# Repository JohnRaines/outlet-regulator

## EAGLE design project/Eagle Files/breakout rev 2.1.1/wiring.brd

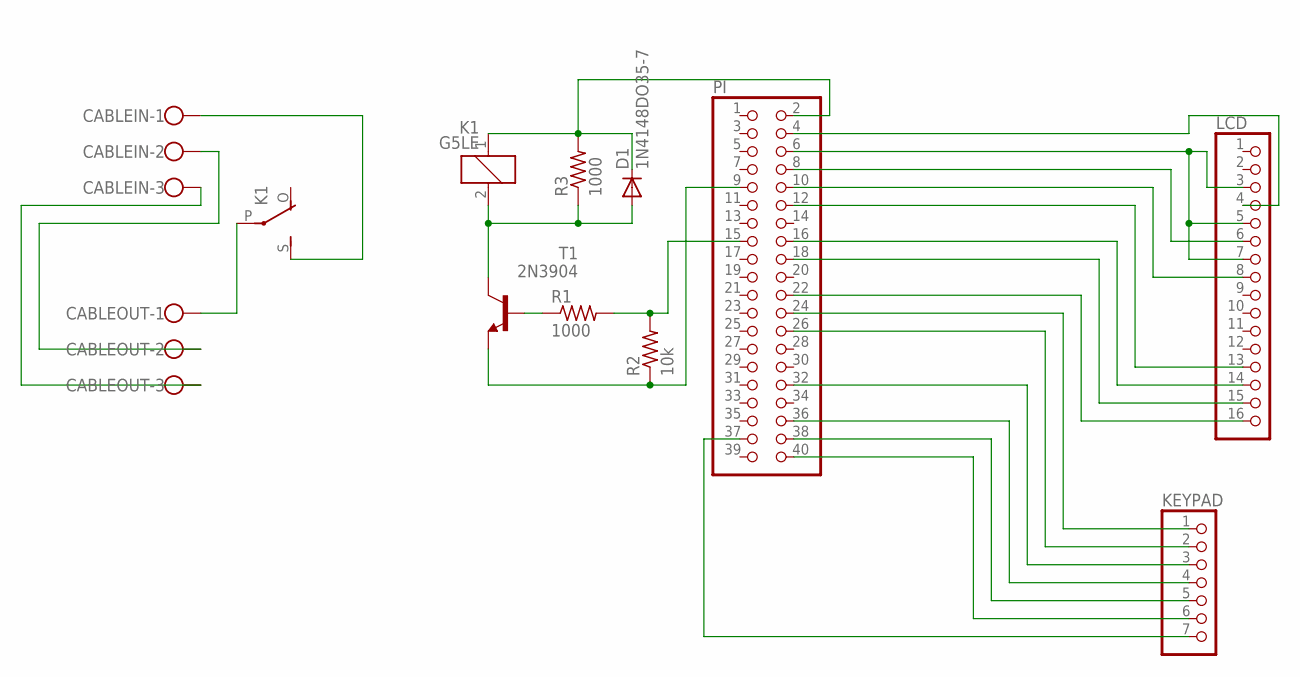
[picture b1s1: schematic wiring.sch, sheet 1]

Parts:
CABLEIN: W237-103
CABLEOUT: W237-103
D1: 1N4148DO35-7; DO35-7
K1: G5LE
KEYPAD: PINHD-1X7; 1X07
LCD: PINHD-1X16; 1X16
PI: PINHD-2X20; 2X20
R1, R3: 1000; 0204/5
R2: 10k; 0204/5
T1: 2N3904; TO92

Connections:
unnamed: CABLEOUT.1, K1.P
unnamed: D1.C, K1.1, PI.2, R3.2
unnamed: CABLEIN.1, K1.S
unnamed: CABLEIN.2, CABLEOUT.2
unnamed: CABLEIN.3, CABLEOUT.3
unnamed: LCD.3, LCD.5, LCD.7, PI.6
unnamed: LCD.4, PI.4
unnamed: LCD.6, PI.8
unnamed: LCD.8, PI.10
unnamed: LCD.14, PI.16
unnamed: LCD.13, PI.12
unnamed: LCD.15, PI.18
unnamed: LCD.16, PI.22
unnamed: KEYPAD.1, PI.24
unnamed: KEYPAD.2, PI.26
unnamed: D1.A, K1.2, R3.1, T1.1 (C)
unnamed: PI.9, R2.1, T1.3 (E)
unnamed: PI.15, R1.2, R2.2
unnamed: R1.1, T1.2 (B)
unnamed: KEYPAD.3, PI.32
unnamed: KEYPAD.4, PI.36
unnamed: KEYPAD.5, PI.38
unnamed: KEYPAD.6, PI.40
unnamed: KEYPAD.7, PI.37

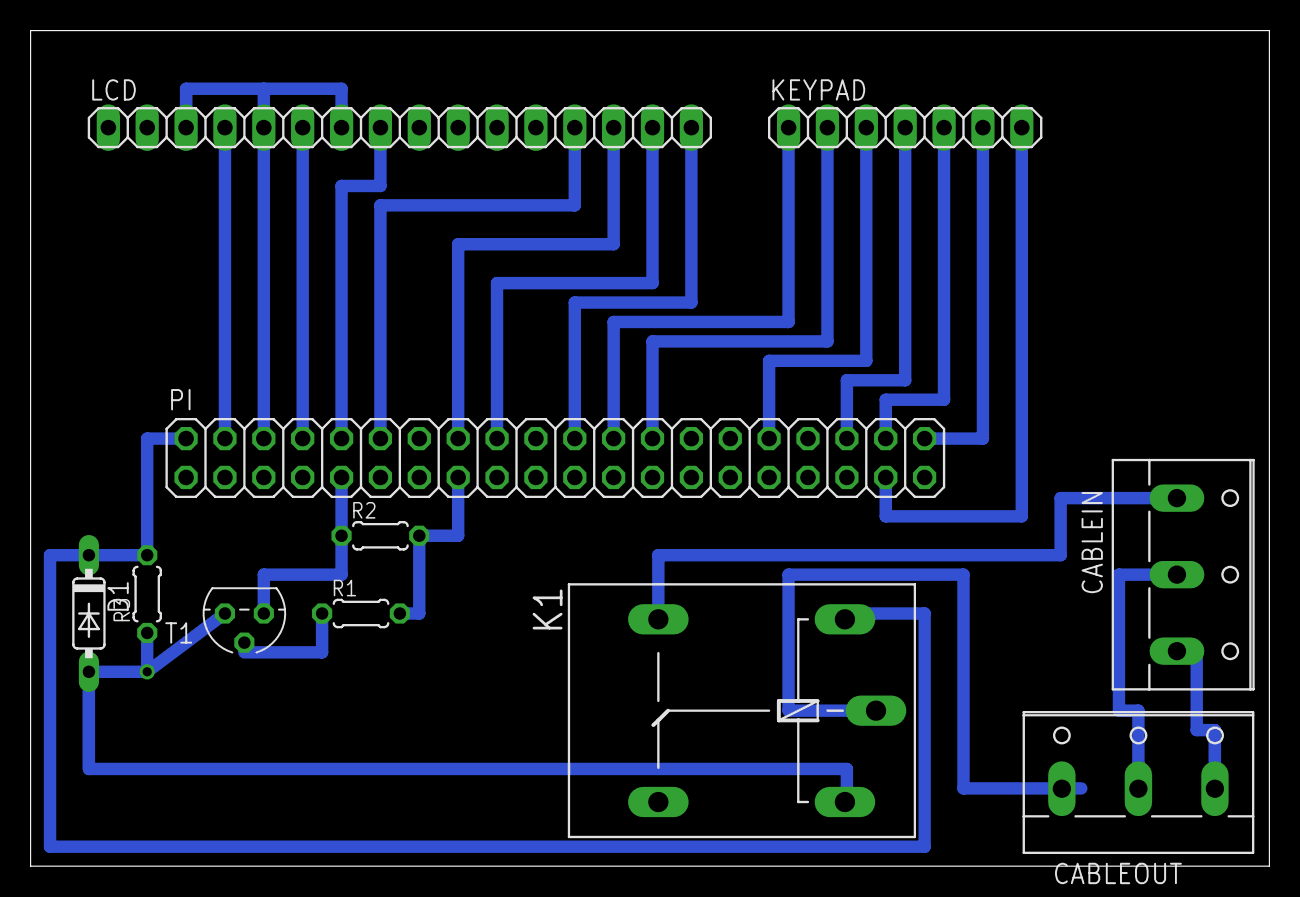
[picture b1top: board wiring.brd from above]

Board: 2 copper layers, 81.0 x 54.6 mm, 11 parts (0 on the bottom side), 24 nets.

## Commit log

2016-11-03 :space_invader: Added .gitattributes & .gitignore files
2016-11-03 Hello world
    repository created and first revision of parts list added
2016-11-03 house keeping
    added general project folder
2016-11-04 Updated parts lis
    added SD card for pi and cleaned up formating
2016-11-06 FIXED TYPO
    Fixed typo where Micro SD card was accidnetally listed as normal SD card
2016-11-21 scp and ssh config guide
    Added a basic guide reflective of my experiences for setting up SSH and
    SCP communication between the pi and a windows machine
2016-11-22 code added
    added the two scripts written so far for the project.
2016-12-14 lcd driver script
    sample lcd driver script being used to test functionality
2016-12-14 updated 14 - 12 - 16
    added the lcd display, the keypad, and removed the arduino
2016-12-14 updated documentation
    added wiring reference for pi and lcd and updated the ssh/scp guide
2016-12-14 added python scripts
    center = current main driver for pi web interface
    web scraper = pulls data from site
    lcd functions = lcd drivers
2016-12-16 updated files
    added wiring guide for keypad and updated python scripts. Center2.py is
    new main app thing
2016-12-29 further refined code
    added functionality for checking monitor state
2017-01-19 Cleaned up documentation
    revised descriptions and, updated center2 for relay driving
    capabilities, and moved obselte code to the "old" folder.
2017-01-19 more cleaning
2017-01-19 commented code
    added some notes about what the code actually does
2017-01-24 Updated everything
    ~changed all code to clean up GPIO layout
    ~added eagle files for second version of pcb
    ~added master pin connection guide
    ~removed redundant txt files
    ~updated parts list
2017-02-02 fixed pcb
    added missing trace that prevented the lcd from working.
2017-02-02 fixed up pcb
    thickened trace that was unintentionally skinny
2017-02-16 updated comments
    I dunno, I actually made these changes so long ago I dont remember what
    I did.
2017-02-16 added stl files for testing bezels
    printer files for the bezels I used to double check the dimensions of the parts
2017-02-16 moved printer files to folder
    I dont know why github's site was acting so weird about making folders
2017-03-07 rar version of files
    asdf
2017-03-07 wrong file type
    asdf
2017-03-07 zip of eagle files
2017-04-18 3d printer files for box
